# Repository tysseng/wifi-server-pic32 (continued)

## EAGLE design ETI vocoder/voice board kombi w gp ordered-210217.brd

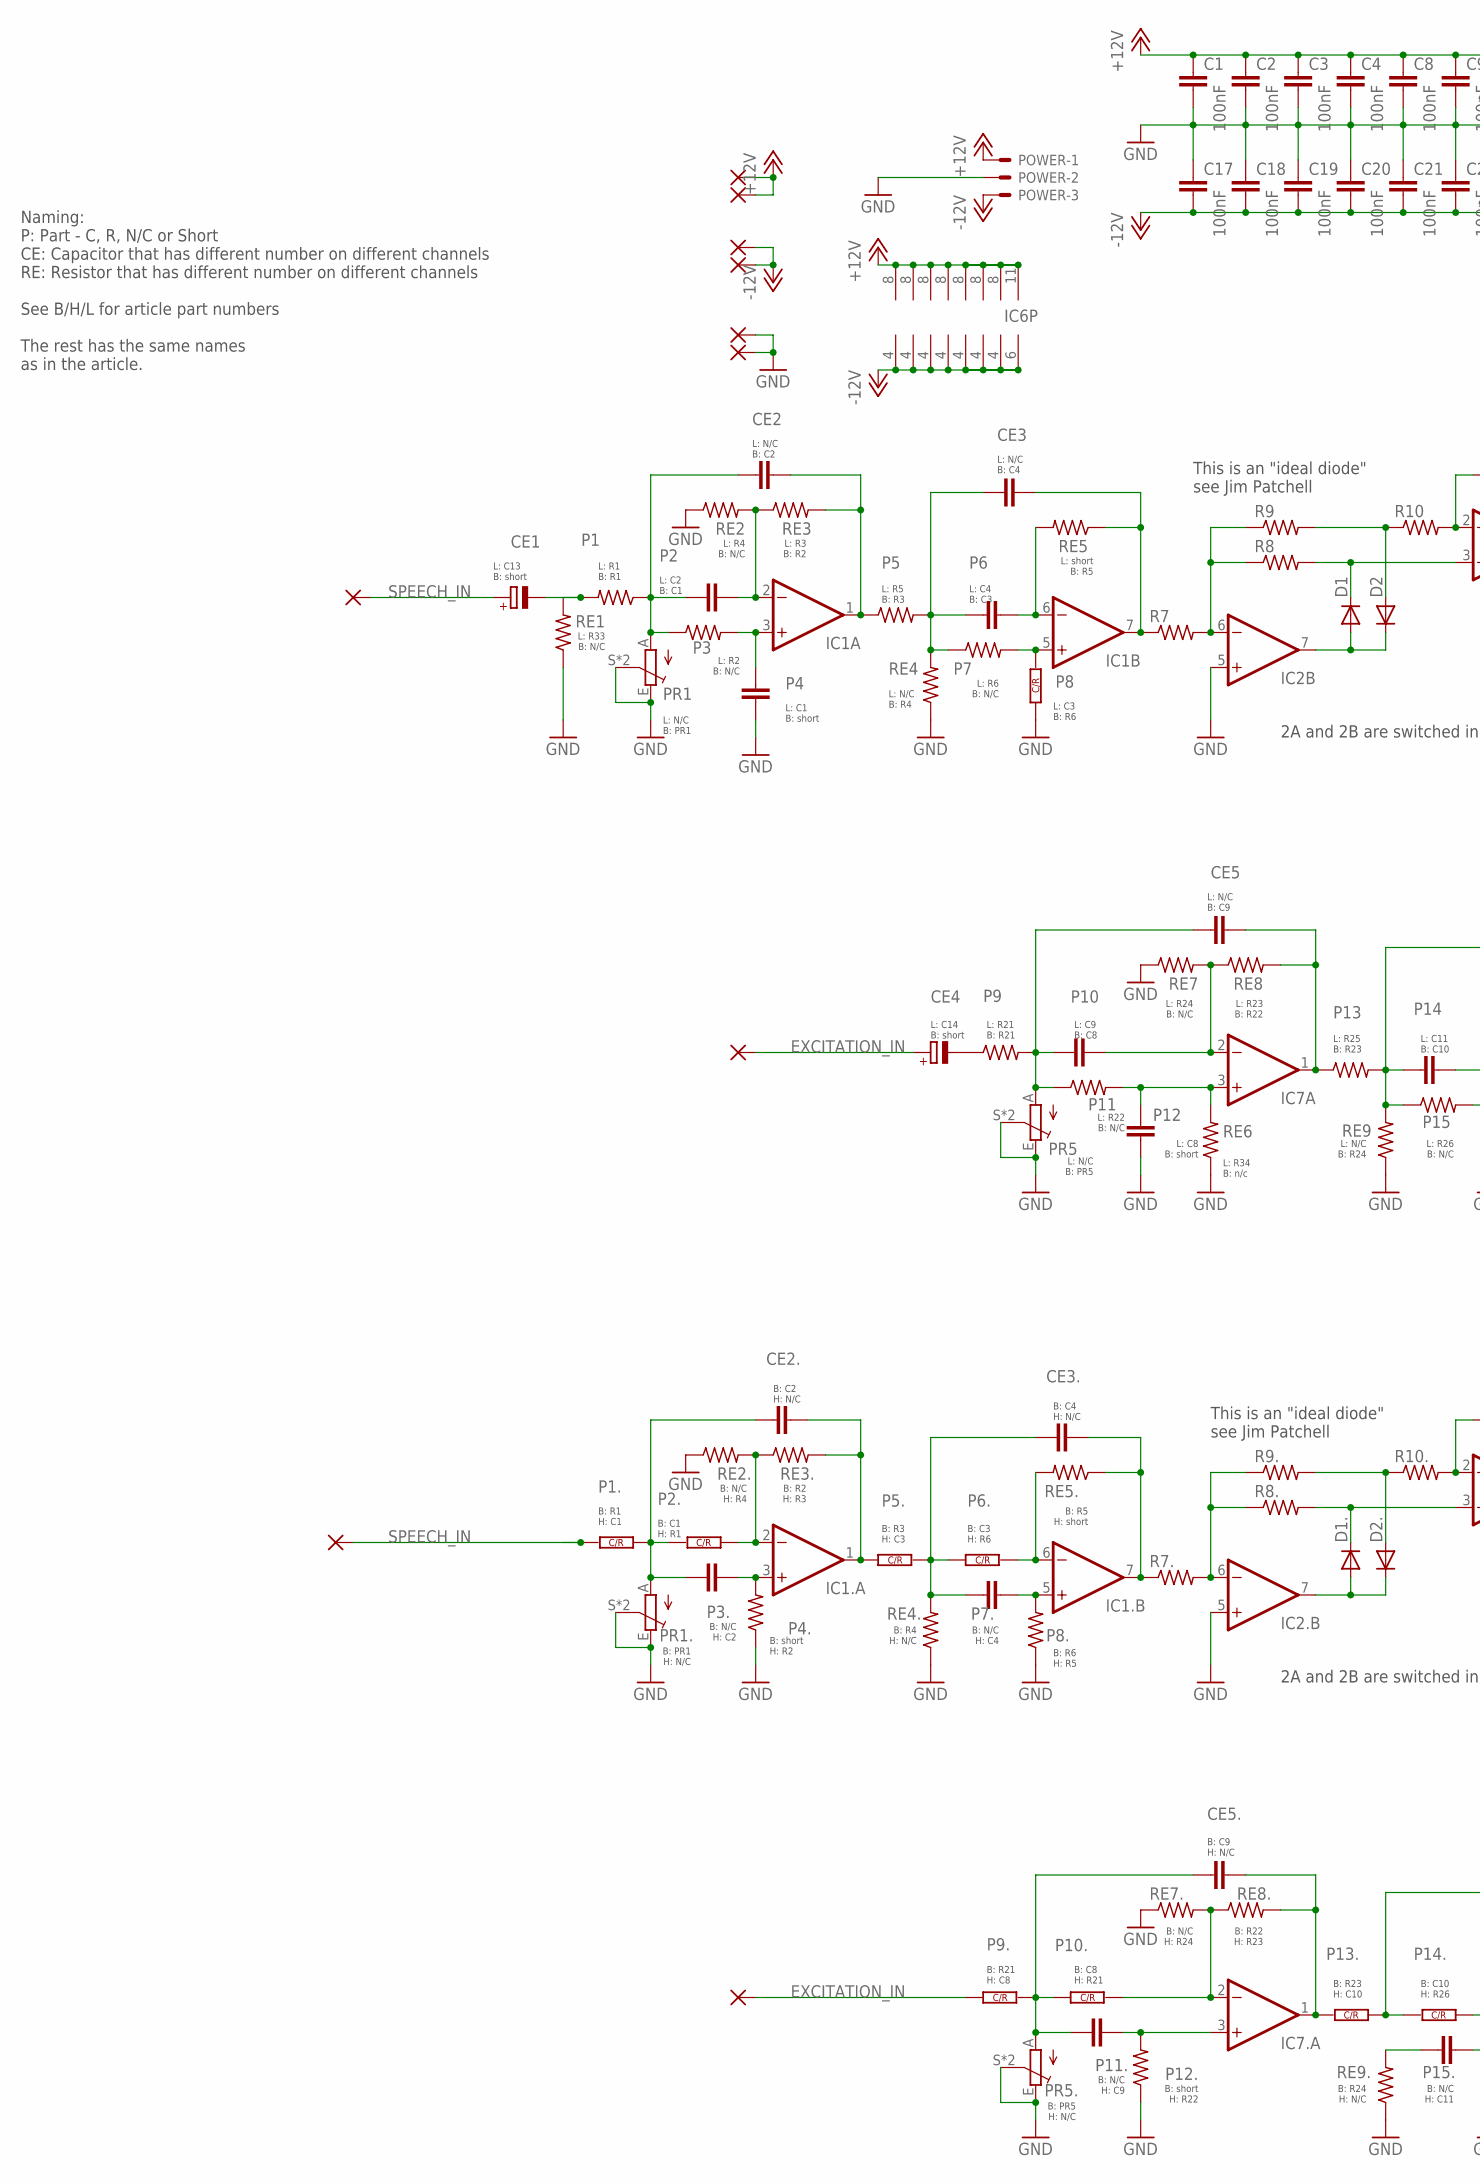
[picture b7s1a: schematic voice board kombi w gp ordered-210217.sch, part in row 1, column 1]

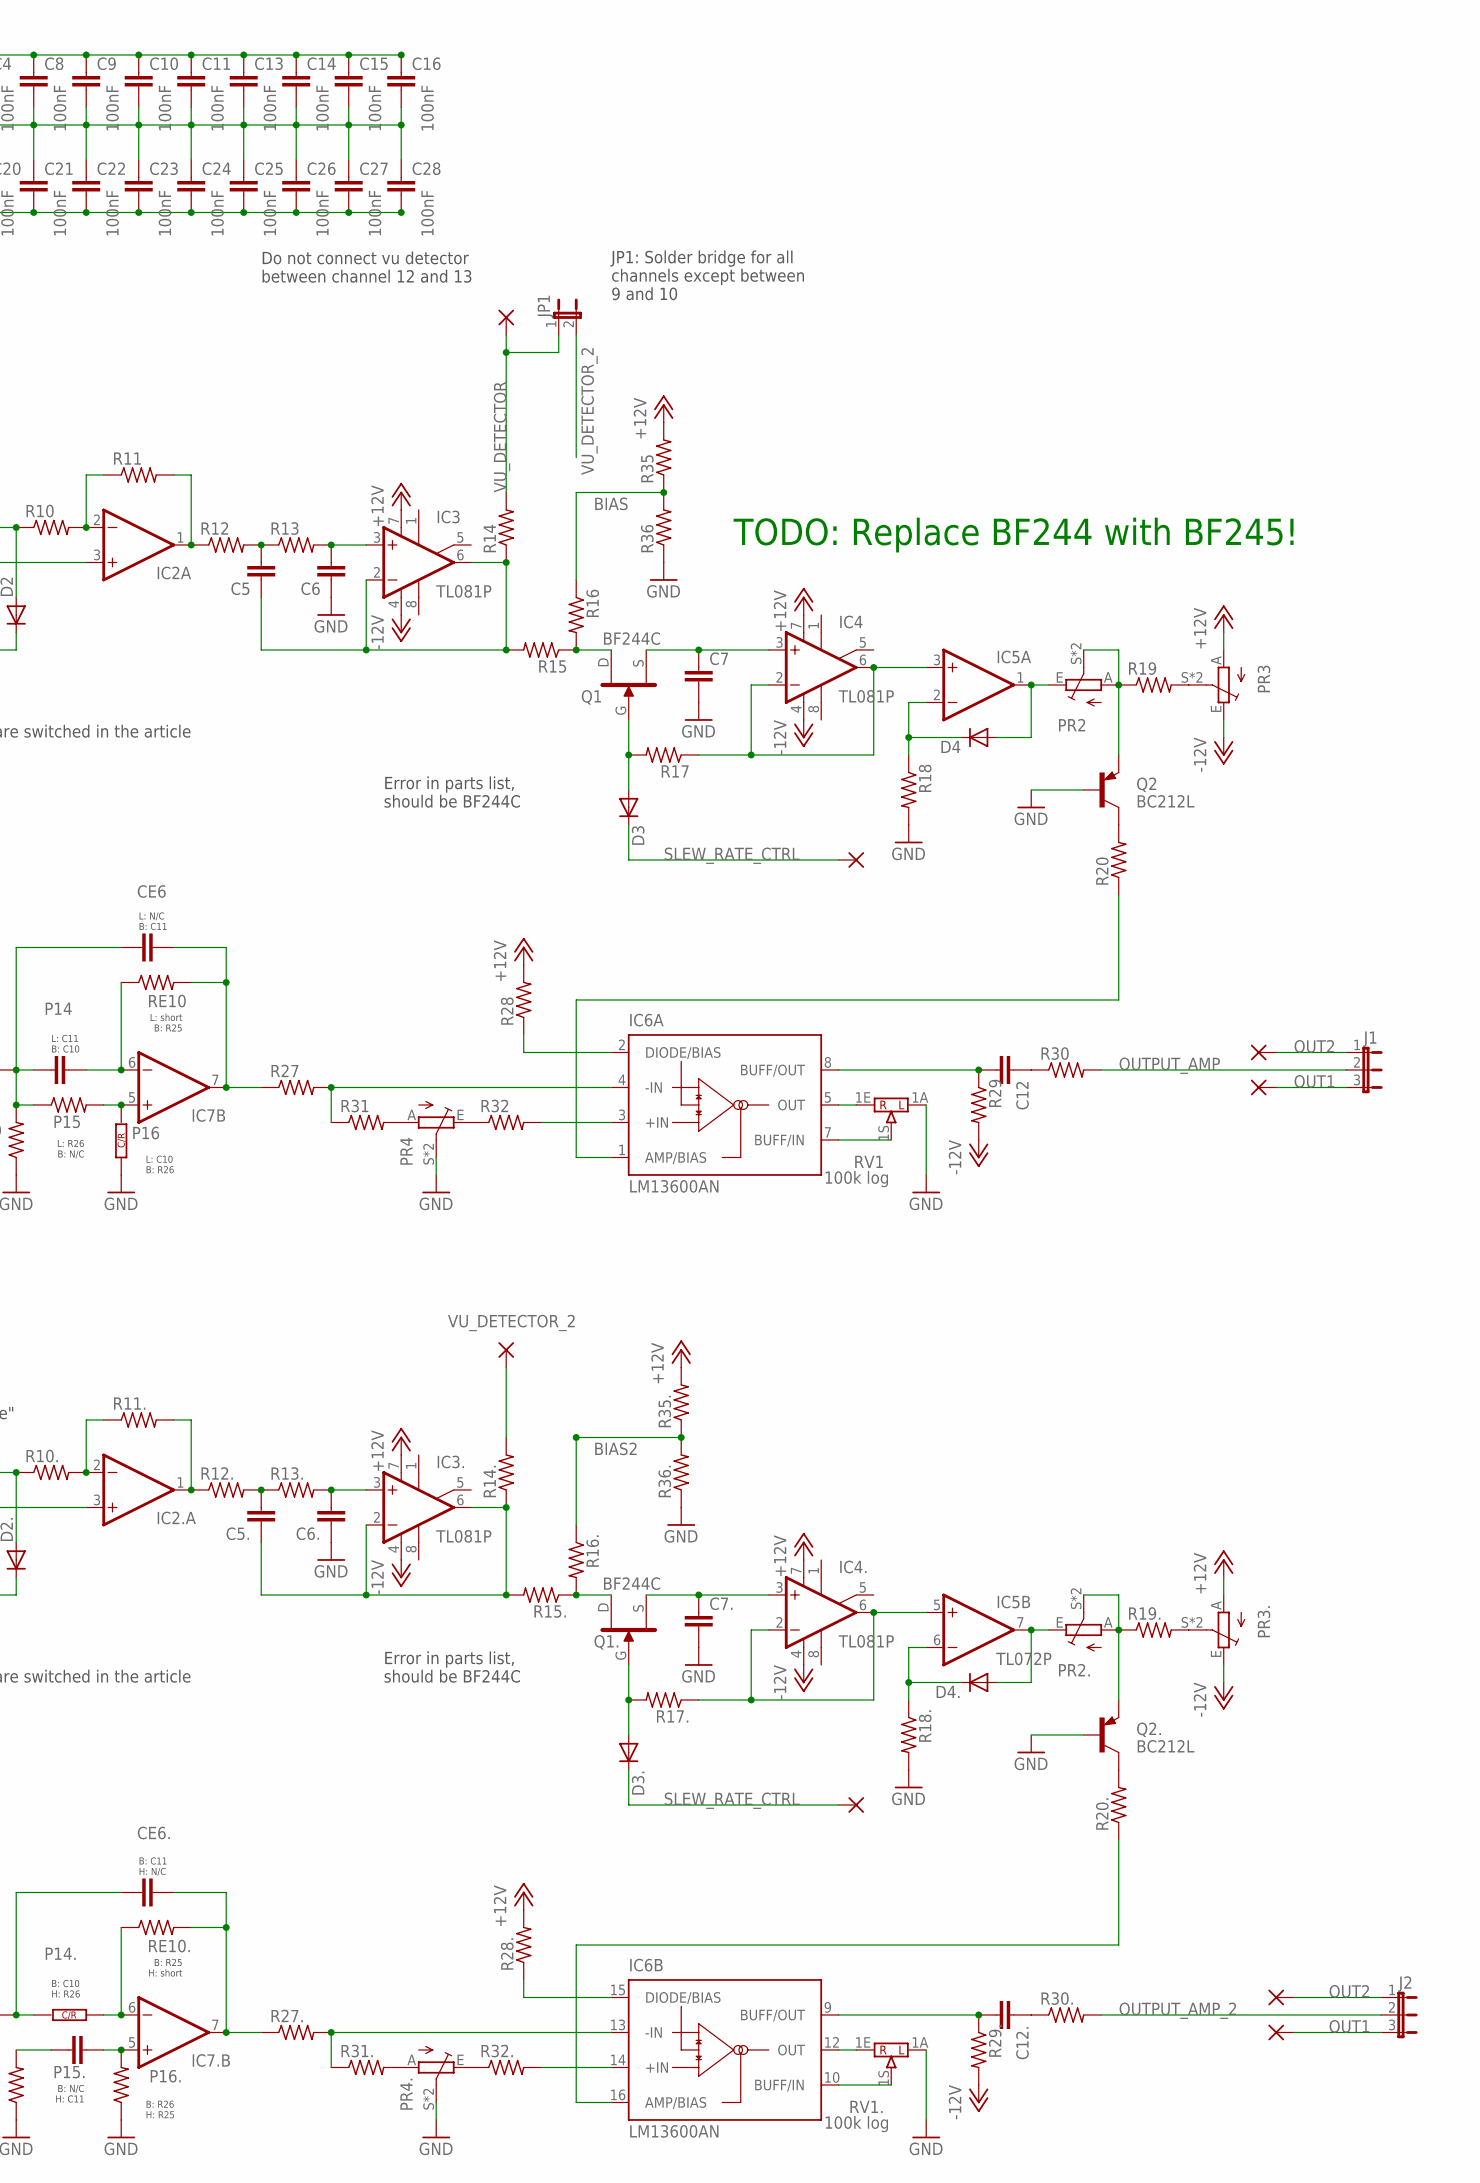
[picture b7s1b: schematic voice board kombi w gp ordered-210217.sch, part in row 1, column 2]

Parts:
C1, C2, C3, C4, C8, C9, C10, C11, C13, C14, C15, C16, C17, C18, C19, C20, C21, C22, C23, C24, C25, C26, C27, C28: 100nF; C0603
C5, C5., C6, C6., C7, C7., C12, C12.: C-EU050-035X075; C050-035X075
CE1, CE4: CPOL-EUE2-4; E2-4
CE2, CE2., CE3, CE3., CE5, CE5., CE6, CE6.: C-EU050-035X075; C050-035X075
D1, D1., D2, D2., D3, D3., D4, D4.: DIODE-D-5; D-5
IC1, IC1., IC2, IC2., IC5, IC7, IC7.: TL072P; DIL08
IC3, IC3., IC4, IC4.: TL081P; DIL08
IC6: LM13600AN; DIL16
J1, J2: JP2E; JP2
JP1: JP1E; JP1
P1, P3, P4., P5, P7, P8., P9, P11, P12., P13, P15, P16.: R-US_0207/7; 0207/7
P1., P2., P5., P6., P8, P9., P10., P13., P14., P16: C-OR-R050_075-035X100; P050_075-035X100J
P2, P3., P4, P6, P7., P10, P11., P12, P14, P15.: C-EU050-035X075; C050-035X075
PAD1, PAD2, PAD3, PAD4, PAD5, PAD6, PAD7, PAD8, PAD9, PAD10, PAD11, PAD12, PAD13, PAD14, PAD15, PAD16, PAD17, PAD18: WIREPAD2,54/1,1; 2,54/1,1
POWER: KK-156-3
PR1, PR1., PR2, PR2., PR3, PR3., PR4, PR4., PR5, PR5.: TRIM_EU-PT10-R065; MULTIPOT_2_J
Q1, Q1.: BF244C; TO92-DGSD-J
Q2, Q2.: BC212L; TO92-ECB
R7, R7., R8, R8., R9, R9., R10, R10., R11, R11., R12, R12., R13, R13., R14, R14., R15, R15., R16, R16., R17, R17., R18, R18., R19, R19., R20, R20., R27, R27., R28, R28., R29, R29., R30, R30., R31, R31., R32, R32., R35, R35., R36, R36.: R-US_0207/7; 0207/7
RE1, RE2, RE2., RE3, RE3., RE4, RE4., RE5, RE5., RE7, RE7., RE8, RE8., RE9, RE9., RE10, RE10.: R-US_0207/7; 0207/7
RE6: R-US_0204/7; 0204/7
RV1, RV1.: 100k log; POT16_W_BRACKET-J

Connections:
+12V: C1.1, C2.1, C3.1, C4.1, C8.1, C9.1, C10.1, C11.1, C13.1, C14.1, C15.1, C16.1, IC1.8 (V+), IC1..8 (V+), IC2.8 (V+), IC2..8 (V+), IC3.7 (V+), IC3..7 (V+), IC4.7 (V+), IC4..7 (V+), IC5.8 (V+), IC6.11 (V+), IC7.8 (V+), IC7..8 (V+), PAD9.1, PAD10.1, POWER.1, PR3.A, PR3..A, R28.2, R28..2, R35.2, R35..2
-12V: C17.2, C18.2, C19.2, C20.2, C21.2, C22.2, C23.2, C24.2, C25.2, C26.2, C27.2, C28.2, IC1.4 (V-), IC1..4 (V-), IC2.4 (V-), IC2..4 (V-), IC3.4 (V-), IC3..4 (V-), IC4.4 (V-), IC4..4 (V-), IC5.4 (V-), IC6.6 (V-), IC7.4 (V-), IC7..4 (V-), PAD13.1, PAD14.1, POWER.3, PR3.E, PR3..E, R29.2, R29..2
BIAS: R16.1, R35.1, R36.2
BIAS2: R16..1, R35..1, R36..2
EXCITATION_IN: CE4.+, P9..1, PAD3.1, PAD4.1
GND: C1.2, C2.2, C3.2, C4.2, C6.1, C6..1, C7.2, C7..2, C8.2, C9.2, C10.2, C11.2, C13.2, C14.2, C15.2, C16.2, C17.1, C18.1, C19.1, C20.1, C21.1, C22.1, C23.1, C24.1, C25.1, C26.1, C27.1, C28.1, IC2.5 (+IN), IC2..5 (+IN), P4.1, P4..1, P8.1, P8..1, P12.1, P12..1, P16.1, P16..1, PAD15.1, PAD16.1, POWER.2, PR1.E, PR1.S, PR1.S0 (S), PR1..E, PR1..S, PR1..S0 (S), PR4.S, PR4.S0 (S), PR4..S, PR4..S0 (S), PR5.E, PR5.S, PR5.S0 (S), PR5..E, PR5..S, PR5..S0 (S), Q2.B, Q2..B, R18.2, R18..2, R36.1, R36..1, RE1.1, RE2.1, RE2..1, RE4.1, RE4..1, RE6.1, RE7.1, RE7..1, RE9.1, RE9..1, RV1.1A, RV1..1A
unnamed: IC1.2 (-IN), P2.2, RE2.2, RE3.1
unnamed: CE2.1, P1.1, P2.1, P3.1, PR1.A
unnamed: CE2.2, IC1.1 (OUT), P5.1, RE3.2
unnamed: IC2.6 (-IN), R7.2, R8.1, R9.1
unnamed: CE3.1, P5.2, P6.1, P7.1, RE4.2
unnamed: IC1.6 (-IN), P6.2, RE5.2
unnamed: IC1.5 (+IN), P7.2, P8.2, P8.3 (2)
unnamed: CE3.2, IC1.7 (OUT), R7.1, RE5.1
unnamed: D1.C, IC2.3 (+IN), R8.2
unnamed: D1.A, D2.C, IC2.7 (OUT)
unnamed: D2.A, R9.2, R10.1
unnamed: IC2.2 (-IN), R10.2, R11.1
unnamed: IC2.1 (OUT), R11.2, R12.1
unnamed: C5.2, R12.2, R13.1
unnamed: C5.1, IC3.2 (-IN), IC3.6 (OUT), R14.1, R15.2
unnamed: C6.2, IC3.3 (+IN), R13.2
unnamed: Q1.D, Q1.D2 (D), R15.1, R16.2
unnamed: C7.1, IC4.3 (+IN), Q1.S
unnamed: D3.A, Q1.G, R17.2
unnamed: IC4.2 (-IN), IC4.6 (OUT), IC5.3 (+IN), R17.1
unnamed: D4.C, IC5.2 (-IN), R18.1
unnamed: D4.A, IC5.1 (OUT), PR2.E
unnamed: PR2.A, PR2.S, PR2.S0 (S), Q2.E, R19.1
unnamed: PR3.S, PR3.S0 (S), R19.2
unnamed: Q2.C, R20.2
unnamed: PR4.A, R31.2
unnamed: CE5.2, P9.2, P10.2, P11.1, PR5.A
unnamed: CE6.2, P13.2, P14.2, P15.1, RE9.2
unnamed: IC7.2 (-IN), P10.1, RE7.2, RE8.1
unnamed: CE5.1, IC7.1 (OUT), P13.1, RE8.2
unnamed: IC7.6 (-IN), P14.1, RE10.1
unnamed: IC7.5 (+IN), P15.2, P16.2, P16.3 (2)
unnamed: C12.2, IC6.8 (BUFF/OUT), R29.1
unnamed: C12.1, R30.1
unnamed: CE6.1, IC7.7 (OUT), R27.1, RE10.2
unnamed: PR4.E, R32.1
unnamed: IC6.3 (+IN), R32.2
unnamed: IC6.2 (DIODE/BIAS), R28.1
unnamed: IC6.4 (-IN), R27.2, R31.1
unnamed: IC6.1 (AMP/BIAS), R20.1
unnamed: IC6.5 (OUT), RV1.1E
unnamed: IC6.7 (BUFF/IN), RV1.1S
unnamed: CE1.-, P1.2, RE1.2
unnamed: IC1.3 (+IN), P3.2, P4.2
unnamed: CE4.-, P9.1
unnamed: IC7.3 (+IN), P11.2, P12.2, RE6.2
unnamed: IC1..2 (-IN), P2..1, RE2..2, RE3..1
unnamed: CE2..1, P1..1, P2..2, P2..3 (2), P3..1, PR1..A
unnamed: CE2..2, IC1..1 (OUT), P5..1, RE3..2
unnamed: CE3..1, P5..2, P5..3 (2), P6..1, P7..1, RE4..2
unnamed: IC1..6 (-IN), P6..2, P6..3 (2), RE5..2
unnamed: IC1..5 (+IN), P7..2, P8..2
unnamed: CE3..2, IC1..7 (OUT), R7..1, RE5..1
unnamed: IC2..6 (-IN), R7..2, R8..1, R9..1
unnamed: D1..C, IC2..3 (+IN), R8..2
unnamed: D1..A, D2..C, IC2..7 (OUT)
unnamed: D2..A, R9..2, R10..1
unnamed: IC2..2 (-IN), R10..2, R11..1
unnamed: IC2..1 (OUT), R11..2, R12..1
unnamed: C5..2, R12..2, R13..1
unnamed: C5..1, IC3..2 (-IN), IC3..6 (OUT), R14..1, R15..2
unnamed: C6..2, IC3..3 (+IN), R13..2
unnamed: Q1..D, Q1..D2 (D), R15..1, R16..2
unnamed: C7..1, IC4..3 (+IN), Q1..S
unnamed: D3..A, Q1..G, R17..2
unnamed: IC4..2 (-IN), IC4..6 (OUT), IC5.5 (+IN), R17..1
unnamed: D4..C, IC5.6 (-IN), R18..1
unnamed: D4..A, IC5.7 (OUT), PR2..E
unnamed: PR2..A, PR2..S, PR2..S0 (S), Q2..E, R19..1
unnamed: PR3..S, PR3..S0 (S), R19..2
unnamed: Q2..C, R20..2
unnamed: PR4..A, R31..2
unnamed: CE5..2, P9..2, P9..3 (2), P10..1, P11..1, PR5..A
unnamed: CE6..2, P13..1, P14..2, P14..3 (2)
unnamed: IC7..2 (-IN), P10..2, P10..3 (2), RE7..2, RE8..1
unnamed: CE5..1, IC7..1 (OUT), P13..2, P13..3 (2), RE8..2
unnamed: CE6..1, IC7..7 (OUT), R27..1, RE10..2
unnamed: PR4..E, R32..1
unnamed: IC6.14 (+IN), R32..2
unnamed: IC6.15 (DIODE/BIAS), R28..1
unnamed: IC6.13 (-IN), R27..2, R31..1
unnamed: IC6.16 (AMP/BIAS), R20..1
unnamed: IC6.10 (BUFF/IN), RV1..1S
unnamed: C12..2, IC6.9 (BUFF/OUT), R29..1
unnamed: C12..1, R30..1
unnamed: IC7..6 (-IN), P14..1, RE10..1
unnamed: IC7..5 (+IN), P15..2, P16..2
unnamed: P15..1, RE9..2
unnamed: IC1..3 (+IN), P3..2, P4..2
unnamed: IC7..3 (+IN), P11..2, P12..2
unnamed: IC6.12 (OUT), RV1..1E
OUT1: J1.3, J2.3, PAD1.1, PAD2.1
OUT2: J1.1, J2.1, PAD17.1, PAD18.1
OUTPUT_AMP: J1.2, R30.2
OUTPUT_AMP_2: J2.2, R30..2
SLEW_RATE_CTRL: D3.C, D3..C, PAD11.1, PAD12.1
SPEECH_IN: CE1.+, P1..2, P1..3 (2), PAD5.1, PAD6.1
VU_DETECTOR: JP1.1, PAD7.1, R14.2
VU_DETECTOR_2: JP1.2, PAD8.1, R14..2

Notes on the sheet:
This is an "ideal diode" see Jim Patchell
L: C13 B: short
L: R1 B: R1
L: N/C B: PR1
L: C2 B: C1
L: N/C B: C2
L: N/C B: C4
L: R3 B: R2
L: R5 B: R3
L: N/C B: R4
L: C4 B: C3
L: C3 B: R6
L: short B: R5
L: R4 B: N/C
L: C1 B: short
L: R2 B: N/C
L: R33 B: N/C
L: R6 B: N/C
2A and 2B are switched in the article
B: R1 H: C1
B: PR1 H: N/C
B: C1 H: R1
B: C2 H: N/C
B: C4 H: N/C
B: R2 H: R3
B: R3 H: C3
B: R4 H: N/C
B: C3 H: R6
B: R6 H: R5
B: R5 H: short
B: N/C H: R4
B: short H: R2
B: N/C H: C2
B: R21 H: C8
B: C8 H: R21
B: R22 H: R23
B: C9 H: N/C
B: C10 H: R26
B: R23 H: C10
B: short H: R22

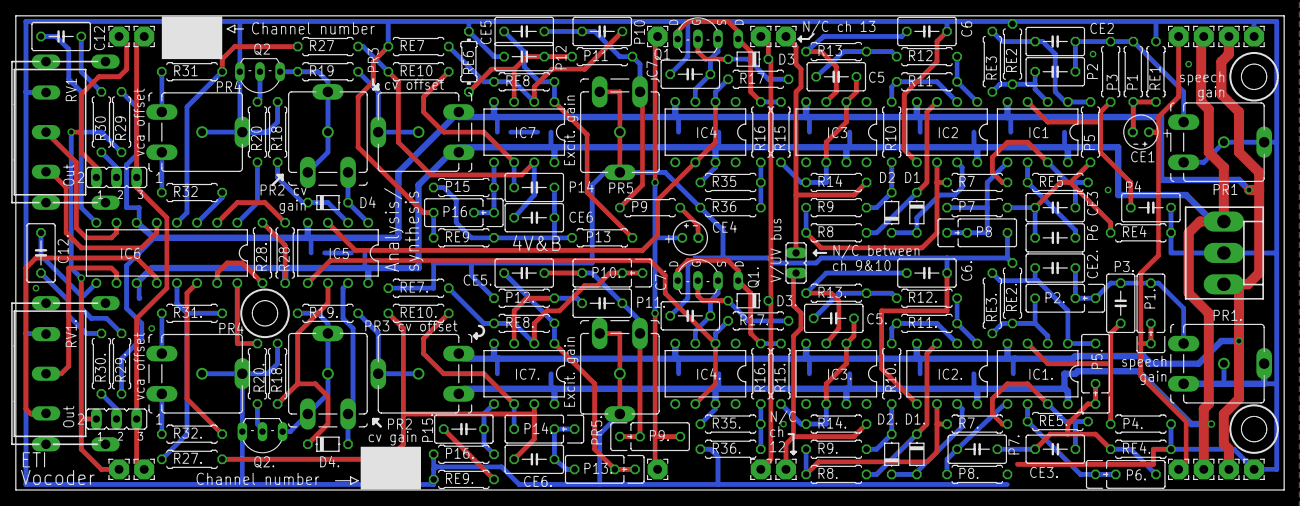
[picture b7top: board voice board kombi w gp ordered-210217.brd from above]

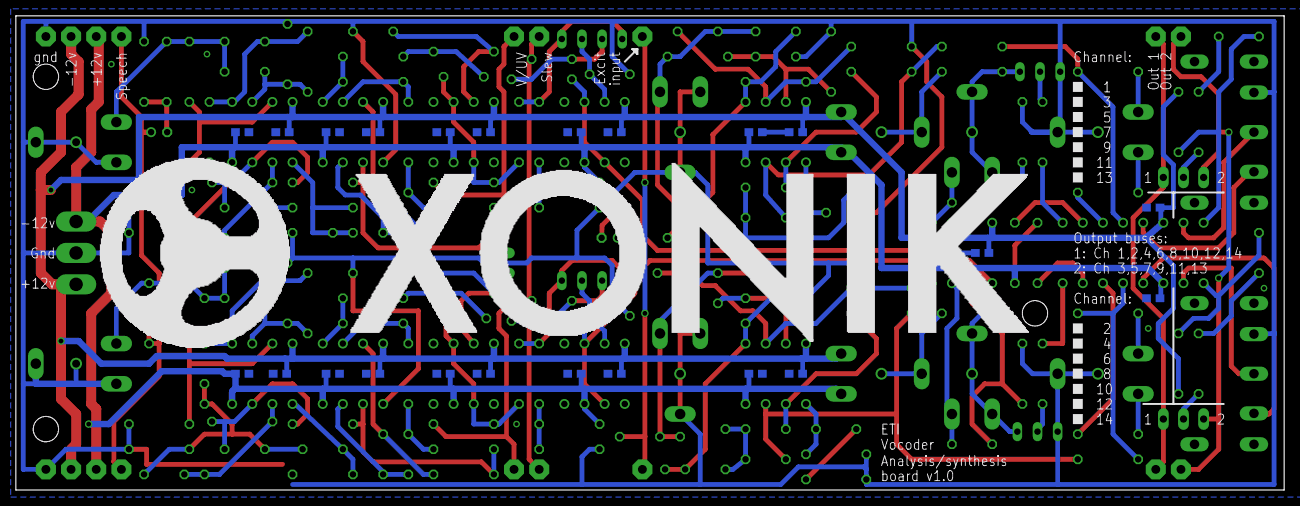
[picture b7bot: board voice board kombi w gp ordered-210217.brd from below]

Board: 2 copper layers, 160.0 x 59.8 mm, 194 parts (24 on the bottom side), 105 nets.

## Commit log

2013-03-08 initial code commit
2013-03-08 code working in OUTPUTMODE_INSTANT_SWITCH mode
2013-03-08 code working in OUTPUTMODE_REVERT_TO_MIDI. Unsure about the rest. switch scanning is a bit dodgy and therefore turned off.
2013-03-09 code ready for prototype (but in little phatty mode)
2013-03-13 Working, now with hanging note protection
2013-03-29 Working on sysex, EE loading of settings
2014-03-02 First commit for frequency counter
2014-03-02 Counter working accurately at 20MHz, from 150Hz to 6.4kHz
2014-03-02 Counter working from 20 to 6000kHz with increased accuracy
2014-03-02 Working on frequency to note converter
2014-03-03 Fully working tuner with octave, semitone, real and wanted frequency displayed. No mismatch indication yet.
2014-04-19 Added so909 source
2014-04-19 Removed build-time files
2014-04-19 cleaning up frequency repo
2015-01-29 Added first version of OMM
2015-01-29 Working minimal version of OMM
2015-01-30 working matrix with several nodes
2015-01-30 working on ramp function
2015-01-31 working ramp up and down
2015-01-31 Working 14 bit dac (MAX544)
2015-02-01 added input, output and delay functions
2015-02-04 improved naming, function pointer lookup
2015-02-04 Added timer for dac and ramps. added binary functions and memory node, working on generalizing integer type for matrix
2015-02-06 dac buffer swapping, initial square lfo implementation, xor, output buffer initialization
2015-02-10 adding MUnit test framework
2015-02-10 added first matrix tests, works like a charm
2015-02-11 Working on LFO test
2015-02-11 added pulse LFO test
2015-02-11 added compare and switch tests
2015-02-12 added more tests
2015-02-13 modified scaling function and added tests
2015-02-13 added all node types, added trigger test
2015-02-18 Added glide node
2015-02-18 added glide to node type switch
2015-02-19 added dac debugging
2015-02-24 Added custom eagle libs
2015-02-27 Started work on exponential converter lookup
2015-04-01 Working 'webserver' that responds on port 80. NB: You have to wait untill you get a DHCP address before trying to access the page (maybe you actually have to try accessing the page before you get one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
2015-04-01 Fully working web server that reacts to request path, turning on and off leds on PORTB
2015-04-01 Code cleanup
2015-04-02 Adding unknown so909-changes to separate branch
2015-04-02 updating mode
2015-04-02 updated .gitignore
2015-04-02 readability improvements
2015-04-02 eagle lib extended
2015-04-03 Working PIC18F slave. Has a strange startup bug and seems to be off by a bit in receiving, debugging next
2015-04-03 SPI master that is able to send data to a PIC18F. The slave picks up a bit weird values, debugging next
2015-04-03 The master sends correct signals (measured using the Saleae logic probe) so the error must be with the slave
2015-04-03 Down to one strange bug - RC3 (LATC.B3) has to be set to 1, or slave won't start. RC3 = SCL. But data is off by one, it starts with a 1 that should not be there and data is offset ('delayed') by one 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
2015-04-03 Fully working PIC18F SPI slave
2015-04-03 Fully working PIC32 SPI master
2015-04-04 Added working PIC18F master with PIC32MX slave. PIC32 does not need the Clock to be set initially
2015-04-04 Added interrupt based slave that only checks input buffer when an rx interrupt is triggered. Enhanced circular buffer reading does not work however
2015-04-05 Added example with interrupts and with slave returning data
2015-04-05 Added PIC32 slave with return
2015-05-15 Updated code to run on the PIC18F25K50 with internal oscillator at 16MHz. Works on the MPG-200 v2.0b
2015-05-16 Fixed sysex support for config. Fixed midi channel rewrite (can be used if JX-3p is not in omni mode and thus receives on midi channel 1 only
2015-05-29 Added ignoring of realtime midi events when in revert-to-midi mode to prevent unnecessary delays
2015-06-01 Changed settings order, added switch boundaries to settings, improved code readability. Created js/html to generate settings sysex. EEprom usage is currently disabled
2015-06-05 Added initial js midi support
2015-06-22 Initial commit, Prophet VS Keyboard Controller, first versions of calculateNoteOnOff and calculateVelocity
2015-06-29 Added test framework and started writing tests
2015-07-07 Finished tests for calcNoteOnOff and calcVelocity. Added sendNoteOns/Offs but without tests
2015-07-08 Added interrupt method, note on/off sending etc. Tests are missing
2015-07-08 added tests for note on, added mocking of ports
2015-07-09 added wait-for-data-to-be-received loop. Removed waiting from tests
2015-07-09 Added interrupt code tests
2015-07-09 Small code improvements
2015-07-09 added init/setup methods for ports etc
2015-07-10 Corrected base note, added volatile to variables updated in both interrupt and main code, added velocity lookup table, removed need for note off-command. Added main loop
2015-07-10 set correct timers, oscillator speed and i/o ports for PIC18F46K80 at 16MHz
2015-07-19 Working webmidi sysex
2015-07-19 added styling and output-test dials
2015-07-22 Sysex received correctly by the mpg200 but changing channel doesn't work
2015-07-23 Flashing led on sysex start and end. Removed mode switch code. Split midi filtering into channel and realtime, fixed bug in filtering that removed sysex end. Fixed bug in javascript that did not send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
2015-07-24 Fixed EE saving and loading of settings
2015-08-03 Added fixes for portB interrupt, bugfixes for turning off analog
2015-08-05 fixed missing pin on porta, added controllable revert to 0 after data send, fixed and started using interrupt based input line
2015-08-13 Working demo, sends c0 on and off every 0.5 seconds. Interrupt on portb working, send working. Scanning not working and some code should be reincluded and tested
2015-08-14 Split into high and low priority interrupts. Moved keyboard scanning out of interrupt routine. Added column counter calibration. Still outputs automatic notes
2015-08-14 Re-added scanning code, works (but with wrong velocity) for the first 8 keys, so something weird with row scanning. Colscan works
2015-08-15 fixed mask increment bug in key sending, but at the same time stopped doing scanning and sending async.
2015-08-15 Fixed timing bug - timer 0 interrupt took too long, changed it into its correct duration to speed it up. Works great
2015-08-30 Removed old overly complex code. Fixed timeout-checking for max key press time. Added tests. Tested live, works (but without velocity)
2015-09-05 4 x speed (64MHz). Velocity calculation works but code has a bug that retriggers notes, probably if key start off bounces
2015-09-05 Fixed hanging notes / prevented noteOn send on startKey bounce
2015-09-06 More efficient and correct timeout prevention/bounce detection. Code is production ready as long as PORTB change events, not interrupts are used
2015-10-11 Working version for 68b01 v1.2
2015-10-11 Updated version for the 68b01 v1.2 with working external interrupt on PB3 instead of PORTB change interrupt, should be slightly safer
2015-10-11 Added web page describing the circuit, for publishing on xonik.no
2016-12-02 ETI vocoder boards
2016-12-02 Added potmeter etc
2016-12-05 Internal excitation schematics
2016-12-12 All ETI boards checked for caps and pots
2016-12-16 Fixed input boards in regards to article and added spacer holes
2016-12-25 Finished first of two halves of the universal voice board
2016-12-27 Duplicated all parts, ready for creating channel 2 (after main computer bailed on me and I lost a days work)
2016-12-28 Finished laying out most duplicated components
2016-12-28 All airwires traced
2016-12-28 Checked and fixed Q2, still need to check cap footprints and shrink board
2016-12-29 Switched to dual footprint caps for all caps (5mm, 7.5mm). Added footprint to custom library
2016-12-29 Replaced all c/r combinations with special component
2016-12-30 Finished (I think) voice boards, added ground planes
2016-12-30 Added logo and did some minor fixes
2016-12-30 Added logo and gp to input and output amps
2017-01-01 Finished combining first board. Moved spline to document layer for potmeter
2017-01-01 Finished second combined board, only missing break-aparts
2017-01-01 Added break-aparts to combined board 2
2017-01-02 Fixed combined 3 and 4, and ordered combined 3
2017-01-08 Send combined 4 to production. Fixed wrong CE1 footprint for voice cards. Removed outline from combined 4 that covered too much of a slot
2017-01-09 Added place to write channel numbers
2017-01-12 Completed DRC and ERC of voice board
2017-01-14 Renamed components to better match parts list from the article. Any part that is not consistent across HP/LP/BP now has either CE, RE or P prefix
2017-01-18 Separated LP/BP from BP/HP channels (left channel is never HP, right is never LP). Removed unused/shorted parts. Replaced all caps with wider ones w. 5mm pitch (may have to make them even wider). Rep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
2017-01-18 Changed all caps and C-or-Rs for 5mm pitch 3mm wide ones
2017-01-19 Finished capacitor spacing tweaks, ic sockets should fit now
2017-01-19 Centered capacitors on resistors for a (hopefully) more tidy look
2017-01-20 Reduced board width to 2.355 inch (59.82 mm), this gives a spacing between boards of 1.1 mm, allowing a slight inaccuracy when mounting the cards next to each other
2017-01-23 Updated trimpot names and positions
2017-01-29 Started writing an errata file after soldering the first board
2017-02-01 Added multi-type potmeter footprint
2017-02-01 Documentation for the ETI vocoder build
2017-02-01 Various updates while working on the real vocoder
2017-02-01 Removed all capacitor footprints not modified by me
2017-02-04 Added an RM065/PT10 combo potmeter footprint
2017-02-05 Added four-legged transistor footprint to allow various JFETs. Changed all caps to 3.5mm wide
2017-02-06 Added missing resistors after soldering combined 3
2017-02-17 Added optional decoupling capacitors. Still need to route and readd groundplanes
2017-02-18 Routed and DRC/ERC'ed bypass caps
2017-02-19 Small cosmetic fixes
2017-02-22 Added ordered voice board
2017-03-22 Fixed wrong value for C11/C15 on internal excitation board (should be 220uF, not 22uF)
2017-04-15 Working on PIC16F based DCO
2017-04-15 Added dac and pic16f for DCO project
2017-04-16 Layout for DCO core completed
2017-04-16 Added two pin connector
2017-04-16 Added two pin connectors to DCO
2017-04-16 Cleanup
2017-04-17 Partially complete layout for DCO with CV control for pulse and sub osc, and separate triangle wave former
2017-07-18 IR3109 filter variations
2017-07-18 added IR6109, BA662, 2SA1015
2017-07-20 Finished JP6 filter
2017-07-20 Added components needed for JP6 filter
2017-08-29 Finished layout of DCO core v1.0
2017-08-29 Larger pin pads
2017-09-25 Initial schematics for waveshaper
2017-09-26 added smd diode
2017-09-27 Working with board layout
2017-09-28 Still doing layout
2017-09-28 Routing complete except for bypass caps
2017-09-29 Finished tracing, working on labels
2017-09-30 one pin connector added
2017-09-30 Trace and text complete, gp and logo missing
2017-10-03 Renamed. Tested 330k resistor and pulse input, updated schematics. Comparison to breadboarded circuit still needed, then only logo and gp is remaining
2017-10-05 Probably final version before adding gp and stuff
2017-10-05 Added ground plane
2017-10-06 Added logo, only panelizing is missing
2017-10-08 Xonik Noise A6 - Andromeda A6 based noise circuit with some values changed
2017-10-09 Routing completed except for error checking.
2018-01-27 Removed subrepos moved to xonik account
2018-01-27 removed omm, moved to xonik.no
2018-01-27 moved to xonik
2018-01-27 moved to separate repo
2018-01-27 last file left
